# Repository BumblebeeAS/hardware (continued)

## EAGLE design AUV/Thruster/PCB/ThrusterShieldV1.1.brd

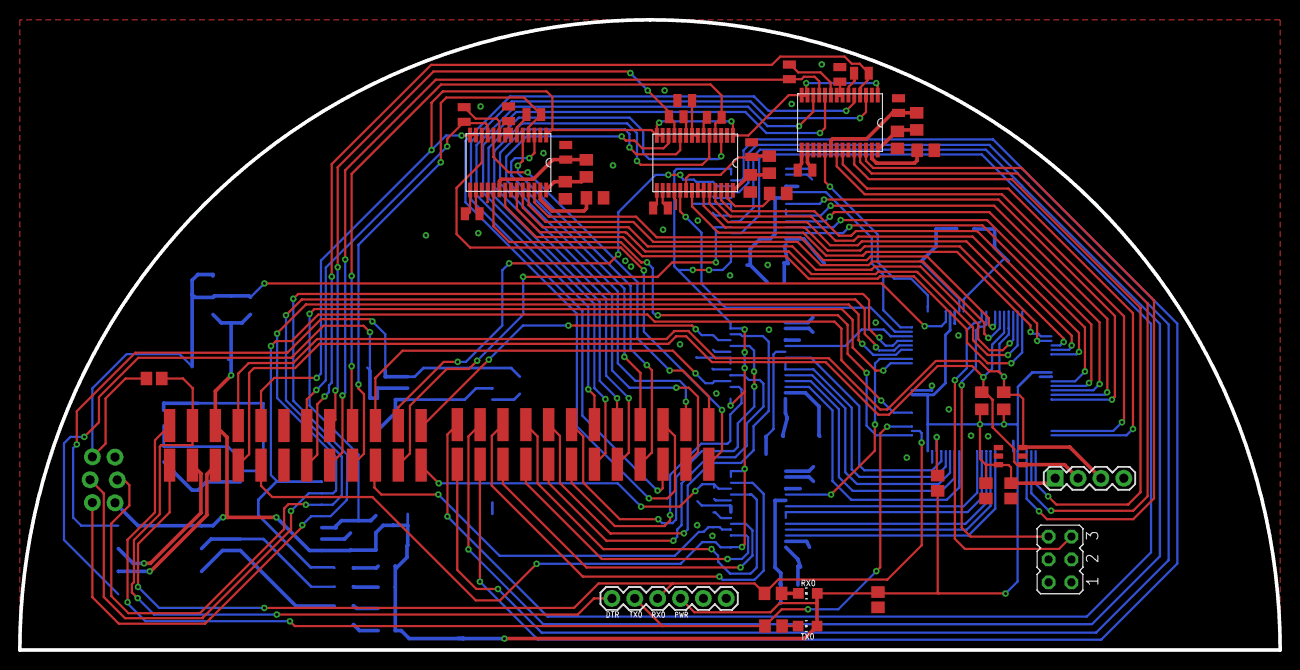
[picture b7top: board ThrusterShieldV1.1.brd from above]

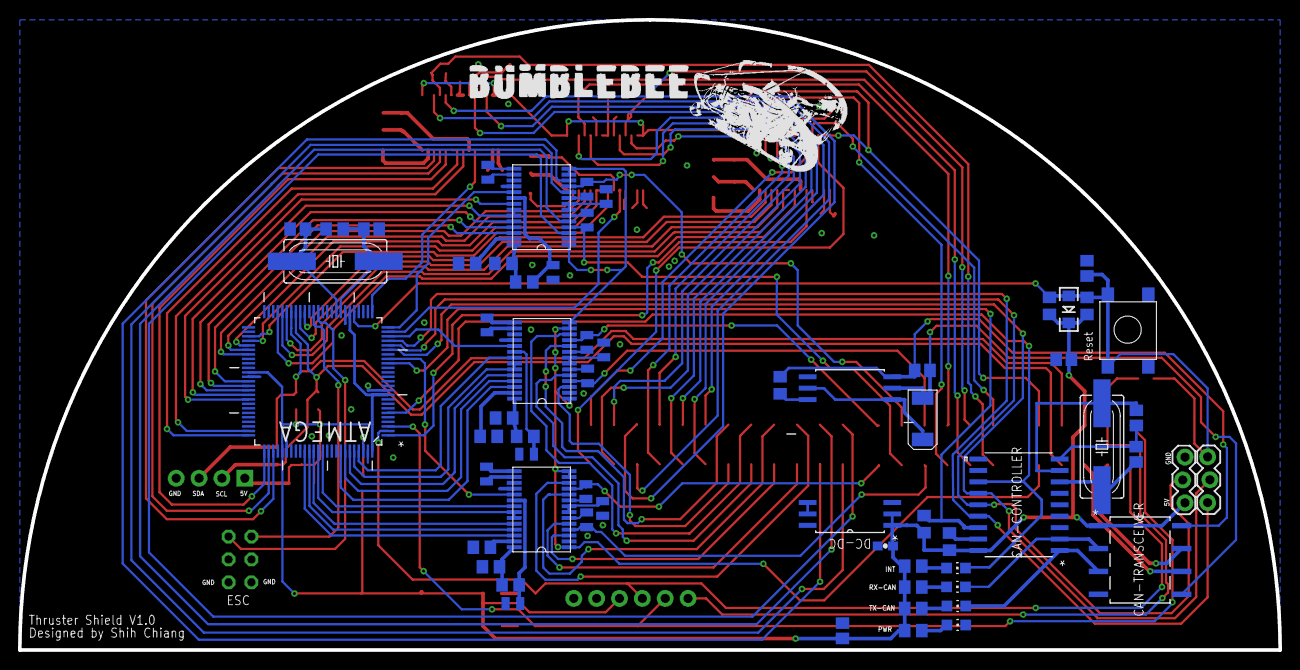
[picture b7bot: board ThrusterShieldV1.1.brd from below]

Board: 2 copper layers, 140.0 x 70.0 mm, 105 parts (61 on the bottom side), 157 nets.

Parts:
16MHZ: HC49UP
ATMEGA: ATMEGA2560-16AU; QFP50P1600X1600X120-100N
C1, C6, C11, C16, C21, C26: 470nF; CAPC2013X70N
C2, C3, C5, C7, C8, C10, C12, C13, C15, C17, C18, C20, C22, C23, C25, C27, C28, C30: 100nF; CAPC2013X70N
C4, C9, C14, C19, C24, C29: 4.7uF; CAPC2013X70N
C33, C42: 0.1uF; C0805
C34: 10uF; C0805
C35, C36, C43, C55: 100nF; C0805
C37: 4.7nF; C0805
C40, C41, C44, C53, C54: 22pF; C0805
C56: 1uF; EIA6032
C57: 2.2uF; 0603-CAP
CAN-CONTROLLER: MCP2515-E/SO; SOIC127P1030X265-18N
CAN-TRANSCEIVER: ISO1050DUBR; SOIC254P1040X485-8N
DC-DC: DCR010505U; SOIC127P1032X265-12NA
INT: CHIP-LED0805
JP1, JP2: 1X03_LOCK
JP3: JP3Q
JP4: 1X06
JP5: 1X04
PWR: CHIP-LED0805
Q2: HC49UP
R1, R8, R15, R22, R29, R36: 47k; R0805
R2, R3, R6, R13, R20, R27, R34, R41, R53, R62, R78, R79, R82: 10k; R0805
R7, R14, R21, R28, R35, R42: 5k; R0805
R58: 1M; R0805
R69, R70, R74, R75, R76, R77: 330; R0805
RX0: CHIP-LED0805
RX-CAN: CHIP-LED0805
SWITCHING-CHIP-DIODE: LED-1206
TX0: CHIP-LED0805
TX-CAN: CHIP-LED0805
U$1, U$2: 15-91-0360
U$4: AD7414; SOT23-6
U$25, U$26, U$27, U$28, U$29, U$30: A3941KLPTR-T; TSSOP-28
U$35: B3FS-1000; B3F2-1000

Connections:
+5V: ATMEGA.10, ATMEGA.31, ATMEGA.61, ATMEGA.80, ATMEGA.100, C33.1, C34.1, C35.1, C36.1, C37.1, C43.1, C57.2, CAN-CONTROLLER.18, CAN-TRANSCEIVER.1, DC-DC.1, DC-DC.2, JP1.3, JP4.VCC, JP5.1, R2.1, R3.1, R53.1, R62.1, R74.1, R75.1, R76.1, R77.1, R78.1, R82.1, RX0.A, SWITCHING-CHIP-DIODE.C, TX0.A, U$1.3, U$4.3
BATT1: U$1.5, U$25.1, U$25.13, U$25.14, U$26.1, U$26.13, U$26.14, U$27.1, U$27.13, U$27.14
BATT2: U$1.17, U$28.1, U$28.13, U$28.14, U$29.1, U$29.13, U$29.14, U$30.1, U$30.13, U$30.14
CANH: CAN-TRANSCEIVER.7, U$1.14
CANL: CAN-TRANSCEIVER.6, U$1.15
D8: ATMEGA.17, CAN-CONTROLLER.16, R82.2
D45: ATMEGA.39, JP3.6
D46: ATMEGA.38, JP3.5
D50: ATMEGA.22, CAN-CONTROLLER.15, JP2.1
D51: ATMEGA.21, CAN-CONTROLLER.14, JP1.2
D52: ATMEGA.20, CAN-CONTROLLER.13, JP2.2
DTR: C42.1, JP4.DTR, U$1.2
FF1A: ATMEGA.77, U$25.25
FF1B: ATMEGA.42, U$26.25
FF1C: ATMEGA.56, U$27.25
FF1D: ATMEGA.64, U$28.25
FF1E: ATMEGA.94, U$29.25
FF1F: ATMEGA.86, U$30.25
FF2A: ATMEGA.78, U$25.26
FF2B: ATMEGA.41, U$26.26
FF2C: ATMEGA.57, U$27.26
FF2D: ATMEGA.63, U$28.26
FF2E: ATMEGA.93, U$29.26
FF2F: ATMEGA.85, U$30.26
GHA1: U$2.19, U$25.10
GHA2: U$2.12, U$26.10
GHA3: U$2.23, U$27.10
GHA4: U$2.13, U$28.10
GHA5: U$2.6, U$29.10
GHA6: U$2.4, U$30.10
GHB1: U$2.10, U$25.5
GHB2: U$2.21, U$26.5
GHB3: U$2.20, U$27.5
GHB4: U$2.2, U$28.5
GHB5: U$2.17, U$29.5
GHB6: U$2.15, U$30.5
GLA1: U$2.7, U$25.12
GLA2: U$2.24, U$26.12
GLA3: U$2.11, U$27.12
GLA4: U$2.14, U$28.12
GLA5: U$2.5, U$29.12
GLA6: U$2.3, U$30.12
GLB1: U$2.22, U$25.3
GLB2: U$2.9, U$26.3
GLB3: U$2.8, U$27.3
GLB4: U$2.1, U$28.3
GLB5: U$2.18, U$29.3
GLB6: U$2.16, U$30.3
GND: ATMEGA.11, ATMEGA.32, ATMEGA.62, ATMEGA.81, ATMEGA.99, C4.2, C5.1, C9.2, C10.1, C14.2, C15.1, C19.2, C20.1, C24.2, C25.1, C29.2, C30.1, C33.2, C34.2, C35.2, C36.2, C37.2, C40.2, C41.2, C44.2, C53.2, C54.2, C57.1, CAN-CONTROLLER.9, CAN-TRANSCEIVER.4, DC-DC.26, DC-DC.27, JP1.1, JP3.1, JP3.2, JP4.GND, JP5.4, PWR.C, R1.1, R7.2, R8.1, R14.2, R15.1, R21.2, R22.1, R28.2, R29.1, R35.2, R36.1, R42.2, U$1.6, U$4.1, U$4.2, U$25.2, U$25.17, U$25.18, U$26.2, U$26.17, U$26.18, U$27.2, U$27.17, U$27.18, U$28.2, U$28.17, U$28.18, U$29.2, U$29.17, U$29.18, U$30.2, U$30.17, U$30.18, U$35.1, U$35.2
GNDBUS: C55.1, C56.P$2, CAN-TRANSCEIVER.5, DC-DC.13
INT: ATMEGA.6, CAN-CONTROLLER.12, INT.C
unnamed: R1.2, U$25.27
unnamed: C1.1, U$25.16
unnamed: C1.2, U$25.15
unnamed: C3.2, U$25.6
unnamed: C2.2, U$25.9
unnamed: C4.1, U$25.7, U$25.8
unnamed: C5.2, R6.1, U$25.20
unnamed: R6.2, R7.1, U$25.28
unnamed: R8.2, U$26.27
unnamed: C8.2, U$26.6
unnamed: C7.2, U$26.9
unnamed: C9.1, U$26.7, U$26.8
unnamed: C6.1, U$26.16
unnamed: C6.2, U$26.15
unnamed: C10.2, R13.1, U$26.20
unnamed: R13.2, R14.1, U$26.28
unnamed: R15.2, U$27.27
unnamed: C13.2, U$27.6
unnamed: C12.2, U$27.9
unnamed: C14.1, U$27.7, U$27.8
unnamed: C11.1, U$27.16
unnamed: C11.2, U$27.15
unnamed: C15.2, R20.1, U$27.20
unnamed: R20.2, R21.1, U$27.28
unnamed: CAN-CONTROLLER.17, R78.2
unnamed: R22.2, U$28.27
unnamed: C18.2, U$28.6
unnamed: C17.2, U$28.9
unnamed: C29.1, U$28.7, U$28.8
unnamed: C16.1, U$28.16
unnamed: C16.2, U$28.15
unnamed: C20.2, R27.1, U$28.20
unnamed: R27.2, R28.1, U$28.28
unnamed: R29.2, U$29.27
unnamed: C23.2, U$29.6
unnamed: C22.2, U$29.9
unnamed: C24.1, U$29.7, U$29.8
unnamed: C21.1, U$29.16
unnamed: C21.2, U$29.15
unnamed: C25.2, R34.1, U$29.20
unnamed: R34.2, R35.1, U$29.28
unnamed: R36.2, U$30.27
unnamed: C28.2, U$30.6
unnamed: C27.2, U$30.9
unnamed: C19.1, U$30.7, U$30.8
unnamed: C26.1, U$30.16
unnamed: C26.2, U$30.15
unnamed: C30.2, R41.1, U$30.20
unnamed: R41.2, R42.1, U$30.28
unnamed: ATMEGA.98, C43.2
unnamed: R69.1, RX0.C
unnamed: R70.1, TX0.C
unnamed: PWR.A, R74.2
unnamed: R75.2, TX-CAN.A
unnamed: R76.2, RX-CAN.A
unnamed: INT.A, R77.2
unnamed: DC-DC.17, R79.2
OSC1: 16MHZ.2, C54.1, CAN-CONTROLLER.8
OSC2: 16MHZ.1, C53.1, CAN-CONTROLLER.7
PHASE1: ATMEGA.26, U$25.19
PHASE2: ATMEGA.1, U$26.19
PHASE3: ATMEGA.24, U$27.19
PHASE4: ATMEGA.25, U$28.19
PHASE5: ATMEGA.23, U$29.19
PHASE6: ATMEGA.18, U$30.19
PWM1: ATMEGA.75, U$25.22, U$25.23
PWM2: ATMEGA.46, U$26.22, U$26.23
PWM3: ATMEGA.54, U$27.22, U$27.23
PWM4: ATMEGA.66, U$28.22, U$28.23
PWM5: ATMEGA.96, U$29.22, U$29.23
PWM6: ATMEGA.88, U$30.22, U$30.23
RES: ATMEGA.30, C42.2, C44.1, JP2.3, R53.2, R62.2, SWITCHING-CHIP-DIODE.A, U$35.3, U$35.4
RESET1: ATMEGA.76, U$25.24
RESET2: ATMEGA.45, U$26.24
RESET3: ATMEGA.55, U$27.24
RESET4: ATMEGA.65, U$28.24
RESET5: ATMEGA.95, U$29.24
RESET6: ATMEGA.87, U$30.24
RX0: ATMEGA.2, JP4.TXO, R69.2, U$1.13
RX-CAN: CAN-CONTROLLER.2, CAN-TRANSCEIVER.2, RX-CAN.C
SA1: C2.1, U$1.20, U$25.11
SA2: C7.1, U$1.7, U$26.11
SA3: C12.1, U$1.8, U$27.11
SA4: C17.1, U$1.11, U$28.11
SA5: C22.1, U$1.12, U$29.11
SA6: C27.1, U$1.24, U$30.11
SB1: C3.1, U$1.19, U$25.4
SB2: C8.1, U$1.21, U$26.4
SB3: C13.1, U$1.9, U$27.4
SB4: C18.1, U$1.23, U$28.4
SB5: C23.1, U$1.10, U$29.4
SB6: C28.1, U$1.22, U$30.4
SCL: ATMEGA.43, JP5.2, R2.2, U$1.16, U$4.4
SDA: ATMEGA.44, JP5.3, R3.2, U$1.4, U$4.6
SR1: ATMEGA.74, U$25.21
SR2: ATMEGA.47, U$26.21
SR3: ATMEGA.53, U$27.21
SR4: ATMEGA.67, U$28.21
SR5: ATMEGA.97, U$29.21
SR6: ATMEGA.89, U$30.21
TX0: ATMEGA.3, JP4.RXI, R70.2, U$1.1
TX-CAN: CAN-CONTROLLER.1, CAN-TRANSCEIVER.3, TX-CAN.C
VBUS: C55.2, CAN-TRANSCEIVER.8, DC-DC.14, R79.1
VREC: C56.P$1, DC-DC.12, DC-DC.16
XTAL1: ATMEGA.34, C40.1, Q2.1, R58.1
XTAL2: ATMEGA.33, C41.1, Q2.2, R58.2

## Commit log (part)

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2016-11-28 Fixed an error naming of library in #include
2016-12-04 Update ASV_can_defines, EB: add thruster speed CAN msg
2016-12-06 Added in Xbee library
2017-03-24 Create V3 of PMB_main code
2017-03-26 Update calibration files for PMB1,2,3 Add LOW_BATT and AUTO_SHUTDOWN to PMB V3
2017-04-17 Revise code as V2.1
2017-06-18 Update calibration for PMBs
2017-06-25 AUV Thruster: Added Tekin calib + Thruster firmware bugfix
2017-12-14 ASV 2.0: Created new folders for ASV 2.0
2017-12-14 Added Torqeedo Power 26-104 Arduino libraries
2017-12-16 Add POKB & Kill Box testing codes, XBEE Lib to ASV 2.0
2017-12-16 Remove all DS_Store Mac OS-specific file
2017-12-17 Add Test Code for RS232
2017-12-19 Add test code for RS232-Xbee sender and rcver
2017-12-19 gitignore: Fixed typo
2017-12-20 ASV2 Telemetry: Fixed test code
2017-12-21 ASV2 Telemetry: Added screen code
2017-12-21 ASV2 Telemetry: Added Frisky library
2017-12-22 ASV2 Telemetry: Added DAC code + resolve thruster & controlmode btw rc & ocs
2017-12-22 POKB-testing: Fixed XBee
2017-12-24 ASV2 POSB: CAN stub to test roscan
2017-12-24 ASV2 POSB: Added ESC code
2017-12-25 ASV2 POSB: Added Battery Code + Control thruster via typing
2018-01-10 ASV2 POKB: Added CAN
2018-02-03 low_batt detection for remote kill and hard kill detection for POKB
2018-02-07 ASV2 POSB: Remap thruster value + Added read ESC stats
2018-02-07 ASV2 POKB: Fix CAN messages
2018-02-09 ASV2 Telemetry: Fixed all heartbeat and stats
2018-02-21 ASV2 Telemetry: added xbee tx to ocs
2018-02-22 updated first version of OCS MCU firmware
2018-02-22 updated folder structure
2018-02-23 ASV2 POSB: Added wind speed sensor code
2018-02-24 ASV2 Telemetry: Found bug that causes MCU to hang, and LCD screen string input to corrupt
2018-02-24 ASV2 Telemetry: Remove useless files
2018-02-24 ASV2 Telemetry: Remove debug statements
2018-02-24 ASV2-CAN: Updated all boards with latest CAN ID
2018-02-25 ASV2 POKB: Added soft estop from OCS
2018-02-25 ASV2-Telemetry: Added CAN_POPB_STATS to CAN messages that are forwarded through control link
2018-02-26 ASV2 POKB: Fix failsafe bug & Remove debug statements
2018-02-26 ASV2 Telemetry: (Before Seatrial) Fix bug
2018-03-14 ASV2 POPB: Fix CAN receiving issues
2018-03-18 ASV 2.0 Telemetry: Fixed bug where OCS, Tele, RC heartbeat not being forwarded to OCS.
2018-03-21 ASV-2 Telemetry: Need to determine if OCS heartbeat is being sent back through XBee from Telemetry. POPB: Tried and tested switching peripherals. Auto-reset of Datalink implemented to prevent mistakes
2018-03-31 30/3 Seatrial fix: Add pin10 pullup to CAN + xbee sniffing
2018-04-05 ASV 2.0 POPB: Updated code to remove debug messages and classify into 2 level of verbose outputs
2018-04-07 organised new marco and update define file
2018-04-09 9/4 Sea trial: Disable tele check SBC heartbeat, POSB check Tele die
2018-04-09 night shift change com no batt
2018-04-11 code deploy for 4/12 sea trial, update: remove bad frsky frame which shud fix the problem of control mode jumping, tele heartbeat is still ignored by posb and tele ignores sbc heartbeat
2018-04-16 ASV-2 POSB: Fixed Battery temperature
2018-04-23 add can msg ids
2018-04-28 added id for sonar trigger
2018-05-01 origin
2018-05-03 AUV 3.99 PCB - Added folder directory and structure
2018-05-06 AUV-3.99 PMB: Updated PMB code to show indicator when its turning off. Since the PMB takes a short amount of time to save the data, this notifies the user to that the PMB is turning off. PMB is now a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
2018-05-06 AUV 3.99 Script: Added uploader script for AUV SBC. RS232 port is /dev/ttyS0, and Quad UART ports are /dev/ttyUSB*. Uploader script is also updated with AUV SBC's static IP and login credentials.
2018-05-07 ASV2 Tele: fixed issue of RC RSSI not calculated correctly
2018-05-11 AUV3.99 Thruster: Reorganised folders
2018-05-12 AUV3.99: Use Thrusters.h for all 8 thrusters
2018-05-12 AUV 3.99 ST: added code for dna pressure, to be tested with whole system
2018-05-13 AUV 3-99 PMB: Updated PMB to have alternating ID. IDs are hardcoded as of now. Voltage, capacity and current data is also being pumped into CAN. Tested and its displaying on the Telemetry screen with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
2018-05-13 AUV 3.99 ST: Fixed led blinking function bug
2018-05-17 refactor tele code
    removed #define serial and #define hang
2018-05-17 AUV3.99: Thruster firmware complete
2018-05-19 AUV 3.99 ST: Updated CAN masking and filter after adding id for DNA stats
2018-05-23 AUV 3.99 PCB: Updated Load Switch control bits to tally with what is stated in the CAN standard
2018-05-24 AUV 3.99 Script: updated script as ruth changed sbc name
2018-05-27 AUV 3.99 ST: updated DNA CAN msg parsing, LED to be tested further
2018-05-27 ASV-2 Telemetry: Added blinking on screen for debug
2018-05-27 ASV-2 OCS: Handle packet size >8 or 0 in case receive incomplete packet + Add OLED screen
2018-05-30 AUV3.99 Thruster: Reversed all thrusters directions
2018-05-31 AUV3.99: Flipped Thrusters 3-8 again thx to CC anyhow feel direction
2018-05-31 ASV 2.0 Tele: latest sea trial tested code
2018-06-07 AUV3.99: 放了简单的骂你葡累的哈克地普咯
2018-06-07 AUV3.99: Replaced while loops with flags
2018-06-10 AUV3.99: Pushed in case need for pooltest. Working over CAN
2018-06-11 AUV3.99: Torpedo delay from 1000 to 400
2018-06-21 AUV3.99: grabber mapped to MANI_2, Tested over CAN, working
2018-06-26 AUV 3.99 ST: Modified CAN LED for software to set led rgb values
2018-07-01 AUV 3.99 ST: Removed fixed colour rgb, retain software select rgb led values
2018-07-01 AUV 3.99 ST: Reconfigure can led msg
2018-09-03 ASV2: Added test code for Radio + incomplete ack
2018-09-06 ASV2 TELE: Removed xbee code in tele and changed all code for new radio (n2420)
2018-09-06 ASV2 tele: fixed bug of reading wrong position of radio mgs buffer
2018-09-07 ASV2 OCS: added script for flashing ocs board
2018-09-07 ASV2 tele: tested tele code on receiving different msges over radio from arduino
2018-09-08 ASV2 TELE: update test code to serial1 and changed buffer from char to uint8_t
2018-09-10 ASV2.0 OCS: Update asv name and add in ocs script
2018-09-10 ASV2 POSB: change code to not ignore tele HB
2018-10-06 ASV 2 CAN and Tele: Update to accomodate manipulator board heartbeat
2018-10-06 AUV 3.99: Add Gripper Folder
2018-10-25 ASV Defines: Update
2018-11-02 ASV 2.0 POKB: Changed XBee functions to radio functions
2018-11-05 ASV 2.0 POKB: Added in function in POKB main code to send Remote Kill dummy message
2018-11-05 ASV 2.0 POKB, Remote Kill: Removed unnecessary comments
2018-11-07 Added LARS working code
2018-11-08 Revert "ASV 2.0 POKB, Remote Kill: Removed unnecessary comments"
    This reverts commit a765292306239c80f93b567826c17a3134dc1b37.
2018-11-08 Revert "ASV 2.0 Remote Kill: Changed Xbee functions to radio functions"
    This reverts commit 0bdebb23bada91d0b52c44809a291ca2c3e1ca6c.
2018-11-08 Revert "ASV 2.0 POKB: Changed XBee functions to radio functions"
    This reverts commit bb7008e834128565ba85a5dbb264e0f6f87e7cd1.
2018-11-10 ASV 2.0 SBC-CAN: Added code for SBC-CAN that ignores spam from ESCs commands
2018-11-14 ASV 2.0 POKB: Added in code for KILL led to light up when kill signal received
2018-11-14 Commented out wind sensor code, add comments regarding POSB v1.5 relay pin in Torqeedo.h
2019-12-16 CAN_V1.0
2020-01-03 Added AUV 4.0 Directory
2020-01-03 Fix Nested List in README
2020-01-04 Added tutorial on how to use printf function in STM32F0
2020-01-04 Added CAN Library
2020-01-05 Updated Acceptance Filter During Initialisation
    Acceptance Filter now must be manually set by the user. Default state of acceptance filter is accept NONE
2020-01-08 Updated SBC-CAN
2020-01-08 Changed UART IO control
2020-01-08 Added Python script for rs232 -> can test
2020-01-10 Use interrupt mode for sbc and can
2020-01-13 Initial TAB Commit
2020-01-16 Update can_lib.h
    Fixed SetMsgFrame bug
2020-01-21 added can inspector
2020-01-29 fixed random hardfault in code
2020-02-03 Working Version 1.0
2021-05-28 Updated SBC-CAN firmware. Fixed bugs related to nested interrupt calls, CAN library, UART start bit false trigger. Added message queue to replace two-pointer circular buffer
2021-06-07 Fixed broken CubeMX project folder
2021-09-02 move pwm update from interrupt to main loop
2021-09-07 rename AUV-3.99 Manipulator_HackDeploy to Actuation and update acutation code for 3.99
2021-10-08 remove screen artifact and add 2dp for pressure
2021-12-03 add auv_4.0_can_def.h library
2022-02-10 Add i2c timeout to fix hanging issue
    change log v1.2
2022-03-11 STB v1.4: Publish stats ASAP (approx 20Hz)
2022-03-17 update actuation code v2.1: working version
2022-03-19 archive TAB STM code
2022-03-19 ASV3 initial commit
2022-03-30 initial commit for can_asv3_defines
2022-04-15 update STB with depth, LED and SBC temp code
2022-05-16 update thruster & actuation board for actuation to run on thruster CAN
2022-05-18 add missing edits for define file for grabber
2022-05-21 fix LCD driver displaying 0s after dp bug
2022-05-26 add LED functionality for screen
2022-06-03 increase stepper delay for grabber - actuation v2.7
2022-06-08 add pmb stm code
2022-06-08 Revert "Merge branch 'master' of github.com:BumblebeeAS/hardware"
    This reverts commit 7dabc8061c8b39e4708a80b649228c5697245113, reversing
    changes made to 230adeff954a7846dd566df1965dccc0d63deffb.
2022-06-08 Revert "Revert "Merge branch 'master' of github.com:BumblebeeAS/hardware""
    This reverts commit 4843debb32a0d79d7bb176eb711995e38a555b18.
2022-06-11 update AUV4 actuation v2.9 for new grabber
2022-06-13 update STB and actuation code
2022-06-19 v2.12: update to Khangs ball dropper
2022-06-22 230622 addresses updated
2022-06-23 auv4: archive old CAN and move auv_4.0_can_def to CAN folder
2022-06-23 Add reference to CAN messaging standards
2022-06-26 add frksy control structure
2022-06-27 Updated CAN msg standards and added firmware for new sensors
2022-06-30 update actuation v2.14 queue can msg & increase dropper delay
2022-07-02 add software PWM led for STB
2022-07-06 update AUV-4 CAN
2022-07-07 Added POPB Test Code (ASV2 POPB Code)
2022-07-07 Added POSB test code directory
2022-07-08 actuator 3.0
    for 4-2 board, with uart and stallguard
2022-07-08 add test code for POKB where remote kill is bypassed
2022-07-13 calibrate stall value for actuation
2022-07-14 re-organisaton main code and libraries for PMB
2022-07-15 add control status
2022-07-15 refactor POKB
2022-07-19 update actautor
2022-08-01 initial commit for ASV-3 ballshotoer
2022-08-04 add power status message, add button functionality and update pin mapping for power control
2022-08-16 fix battery & frsky bugs in telem
2022-08-16 difix stats display bugs
2022-08-17 changed test code to kill when frsky timeout
2022-08-17 Added frsky timout kill to main code Phantom kill occurs due to button being phantomly triggered. So increase trigger value to 1500. Occassionally detected RSSI Timeout, so made it detect 20 timeout 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
2022-08-17 added frsky kill timeout 2 issues: phantom button press, random frsky timeout phantom button press -> increase detection from 1000 to 1500 random frsky timeout -> 20 timoeout in a row
2022-08-19 add kill info + fix batt stats
2022-08-19 Changed POKB to updated CAN Standards
2022-08-19 fix bug
2022-08-22 fix kill bugs
2022-09-02 Initialise Light Panel Folder
2022-09-18 added posb hb timeout to pokb
2022-09-20 New popb code
2022-09-28 add working standalone code
    needs to bring in CAN
2022-10-04 Initial Commit for OCS Kill
2022-10-09 integrate actuated hydrophone
2022-10-09 Added more ESC stats
2022-10-09 added ESC config files
2022-10-10 POKB file cleaned up
2022-10-10 add ocs kill status on telem screen
2022-10-16 implemented timeout
2022-10-18 debug esc
2022-10-18 Added Remote Kill Bit to receive from both OCS and Remote Kill.
2022-10-18 Commented out code for ESC Control via CAN
2022-10-19 telem add radio + fix esc hb
2022-10-31 initial commit for ASV 3-2 Ballshooter
2022-11-02 add serial control for ballshooter
2022-11-03 edit command sequence
2022-11-07 calibrate linear actuator
2022-11-11 relay control
2022-11-11 off batt
2022-11-13 ballshooter local update
2022-11-13 update toggle
2022-11-15 dtls changes
2023-02-02 added extern variable to inc files to allow for project to build
2023-02-02 Decided not to use radio kill
